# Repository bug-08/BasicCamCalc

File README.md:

Code is in the .ino file. 
The rest are PCB files

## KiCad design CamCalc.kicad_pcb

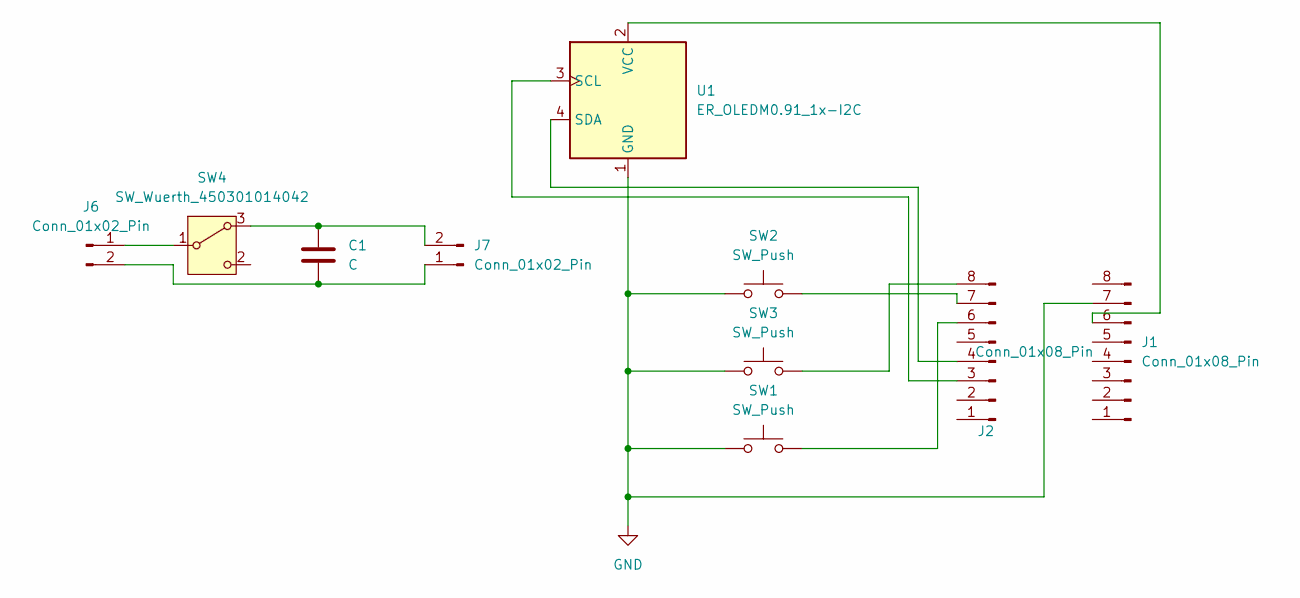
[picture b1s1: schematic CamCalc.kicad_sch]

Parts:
C1: C; CP_Radial_D5.0mm_P2.00mm
J1, J2: Conn_01x08_Pin; PinHeader_1x08_P2.54mm_Vertical
J6, J7: Conn_01x02_Pin; PinHeader_1x02_P2.54mm_Horizontal
SW1, SW2, SW3: SW_Push; FlatSwitch
SW4: SW_Wuerth_450301014042; SW_Slide-03_Wuerth-WS-SLTV_10x2.5x6.4_P2.54mm
U1: ER_OLEDM0.91_1x-I2C

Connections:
GND: J1.7, SW1.1, SW2.1, SW3.1, U1.1 (GND)
unnamed: J1.6, U1.2 (VCC)
unnamed: J2.3, U1.3 (SCL)
unnamed: J2.4, U1.4 (SDA)
unnamed: J2.6, SW1.2
unnamed: J2.7, SW2.2
unnamed: J2.8, SW3.2
unnamed: J6.1, SW4.1 (B)
unnamed: C1.2, J6.2, J7.1
unnamed: C1.1, J7.2, SW4.3 (A)

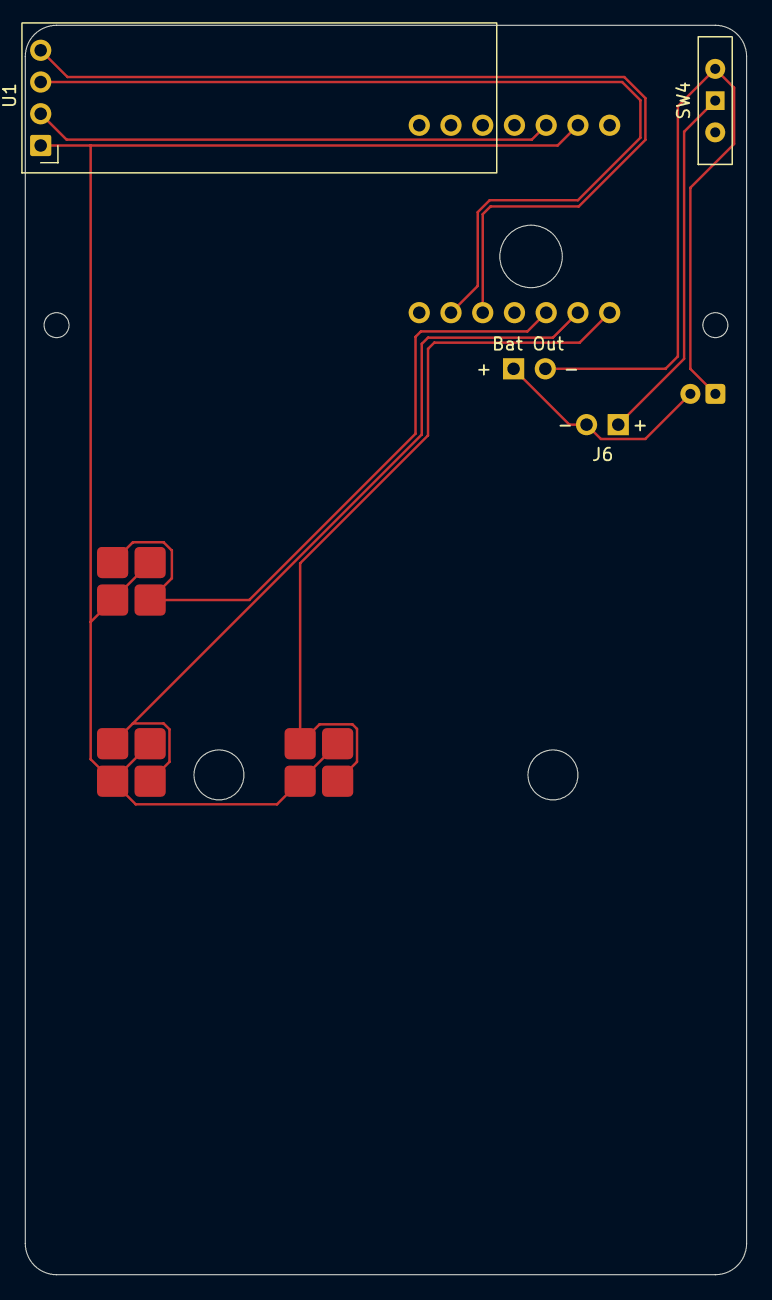
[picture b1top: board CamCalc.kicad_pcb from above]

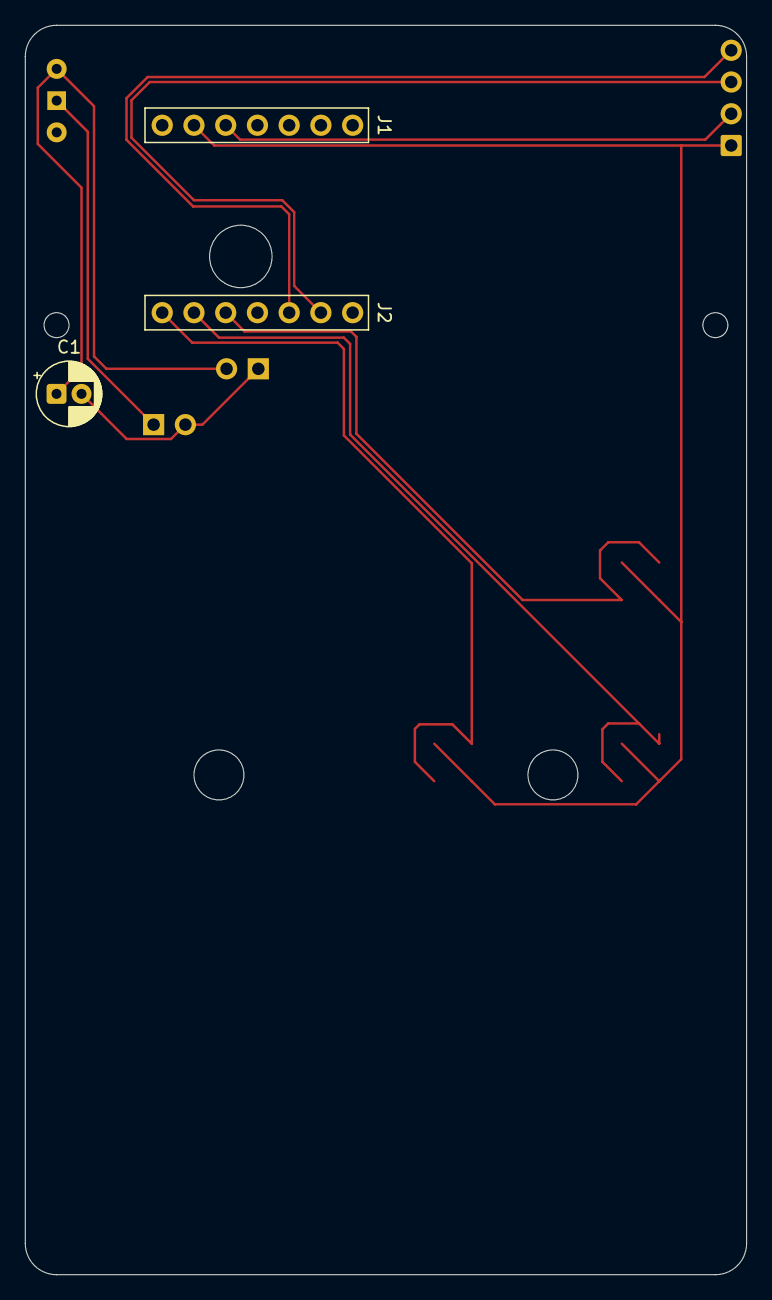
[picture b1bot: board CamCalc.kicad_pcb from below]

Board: 2 copper layers, 57.7 x 100.0 mm, 10 parts (3 on the bottom side), 10 nets.
